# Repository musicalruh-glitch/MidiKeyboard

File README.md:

### **MIDI Keyboard**

This is my MIDI Keyboard, as per the guide from Halflife! The file called "Production" has everything necessary for JLCPCB production. As for the rest of the files, the one that end in _pcb is my PCB, _sch is my schematic, and _pro is the whole project. 

 ### **!!IMPORTANT!!**

I'm extremely sorry for the reviewers, my sister took my computer and posted a kindness reel for my closing reel, and she messed up a lot of stuff and I had to hassle with her a lot, so there wasn't a lot of time to submit properly.

Some pictures of my work:

I gave myself a challenge, for each Hack Club hardware design I make, I'll try to incorporate the Undertale hearts somehow on my PCB's! (Maybe only for Halflife actually..)
I ran into huge problems routing for this project, but I really learned a lot more than I thought I would from it. Hopefully things work out.

### **Here's what each part does!**

1. Waveshare ESP32-S3 Zero (Microcontroller)
   - This is just the microcontroller of the board, it processes the inputs and runs custom code.
2. Kalih Choc Low-Profile Switches x3
   - These are the tactile mechanical keys for the MIDI!!
3. SK6812MINI-E Addressable RGB LEDs x3
   - These are small smart lights, I'm going to solder these to the back of the PCB and they'll shine up through my board's custom cutout holes to provide glowing, customizable underglow backlighting.
4. EC11 Rotary Encoder
   - This is a dial knob that can also be pushed down like a button, awesome for adjusting volume + changing parameters or just scrolling through menus!! :D
5. Bourns Slide Potentiometer
   - This is a sliding fader knob, it connects to an analog pin to continuously measure its exact physical position making it perfect for smooth volume fades, modulation, or filter sweeps.
6. Custom 7-Pad Capacitive Touch Keys
   - This is my custom Undertale soul-heart touch interface. These copper touch pads register the electrical capacitance of my fingertips when I touch them, giving me extra touch-sensitive keys.

### **MIDI Keyboard Project Bill of Materials (BOM)**

| Part / Description | Qty | Unit Price | Total Price | Vendor | Link |
| --- | --- | --- | --- | --- | --- |
| **Custom MIDI Keyboard PCB** (Fabricated circuit board) | 1 | blank | blank | JLCPCB | blank 

* **Total Tax & Shipping for the whole order:** blank

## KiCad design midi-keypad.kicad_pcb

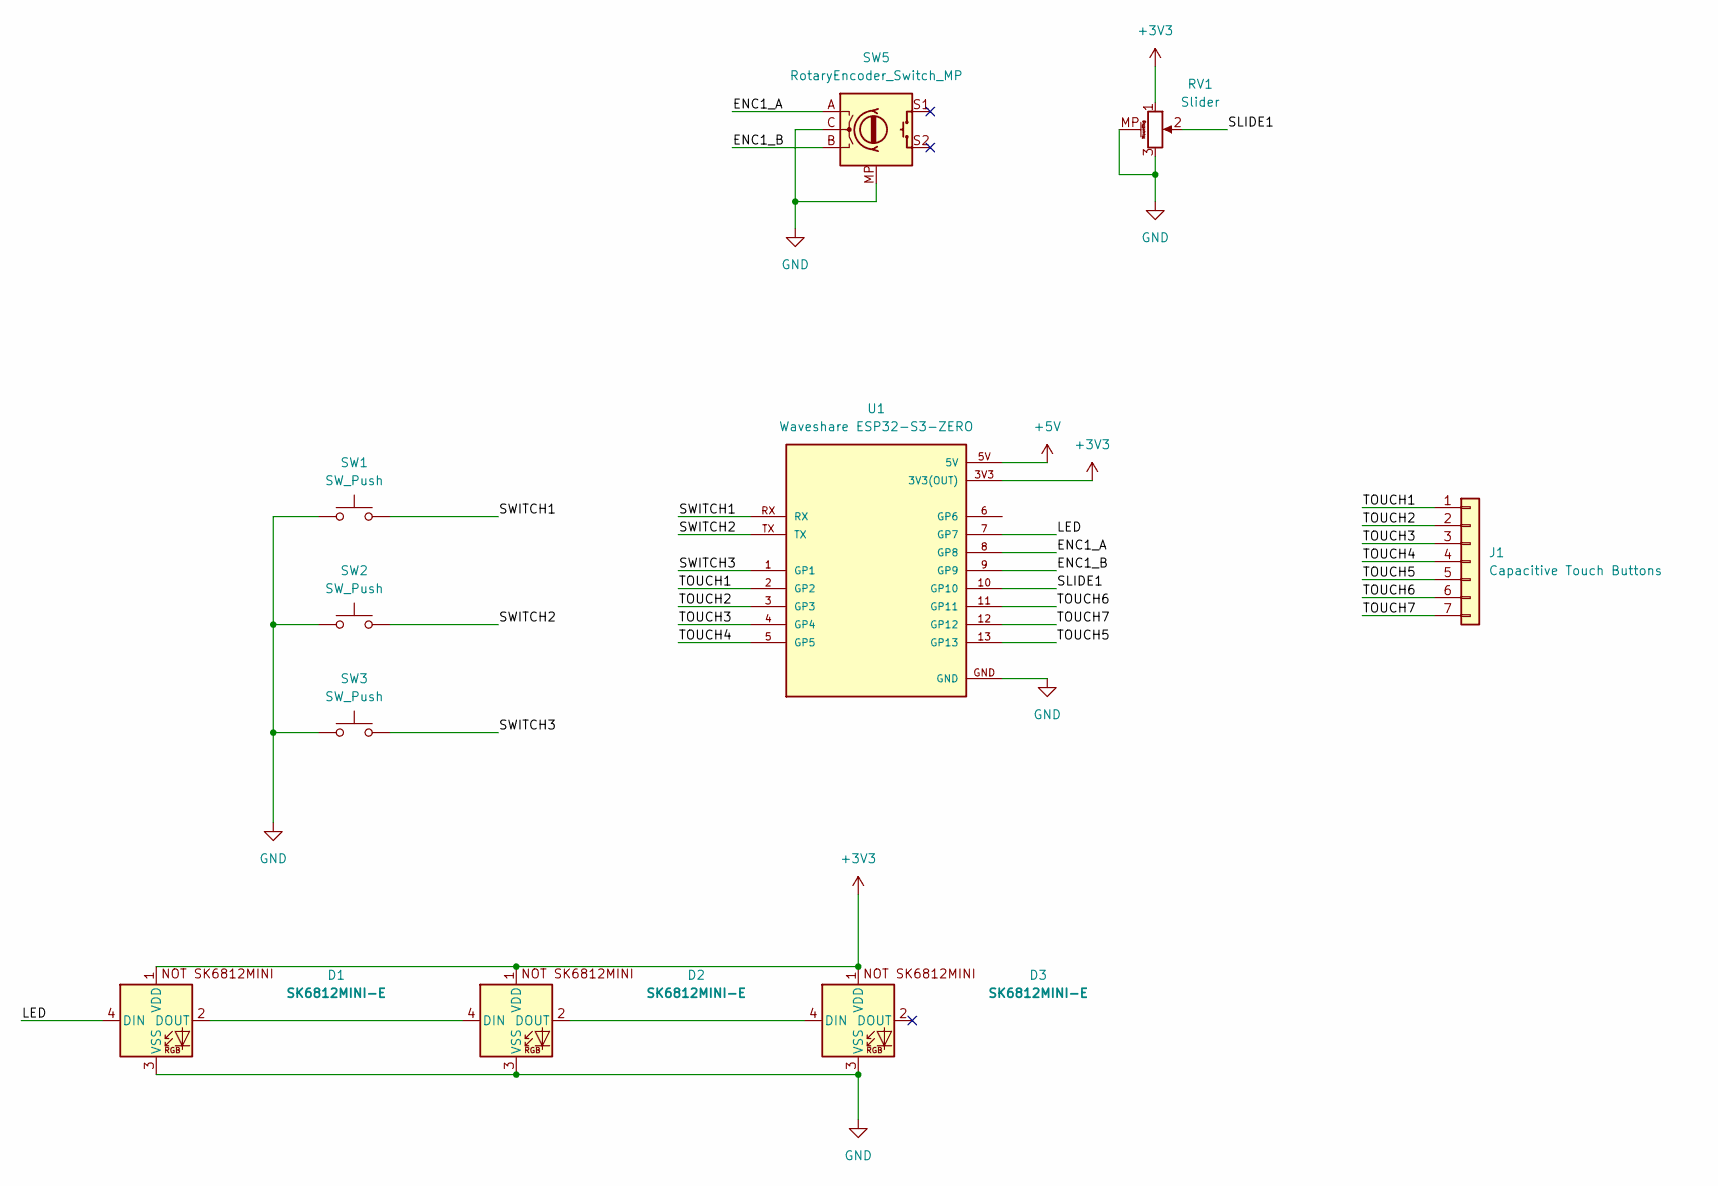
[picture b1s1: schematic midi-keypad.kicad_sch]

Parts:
D1, D2, D3: SK6812MINI-E; LED_SK6812MINI-E_3.2x2.8mm_P1.5mm_ReverseMount
J1: Capacitive Touch Buttons; CapacitiveKeys
RV1: Slider; Potentiometer_Bourns_PTA1543_Single_Slide
SW1, SW2, SW3: SW_Push; Kailh Choc Low-Profile Switches
SW5: RotaryEncoder_Switch_MP; RotaryEncoder_Alps_EC12E-Switch_Vertical_H20mm
U1: Waveshare ESP32-S3-ZERO; Waveshare ESP32-S3-Zero; PARTREV NA

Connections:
+3V3: D1.1 (VDD), D2.1 (VDD), D3.1 (VDD), RV1.1, U1.3V3 (3V3(OUT))
+5V: U1.5V
/ENC1_A: SW5.A, U1.8 (GP8)
/ENC1_B: SW5.B, U1.9 (GP9)
/LED: D1.4 (DIN), U1.7 (GP7)
/SLIDE1: RV1.2, U1.10 (GP10)
/SWITCH1: SW1.2, U1.RX
/SWITCH2: SW2.2, U1.TX
/SWITCH3: SW3.2, U1.1 (GP1)
/TOUCH1: J1.1, U1.2 (GP2)
/TOUCH2: J1.2, U1.3 (GP3)
/TOUCH3: J1.3, U1.4 (GP4)
/TOUCH4: J1.4, U1.5 (GP5)
/TOUCH5: J1.5, U1.13 (GP13)
/TOUCH6: J1.6, U1.11 (GP11)
/TOUCH7: J1.7, U1.12 (GP12)
GND: D1.3 (VSS), D2.3 (VSS), D3.3 (VSS), RV1.3, RV1.MP (MountPin), SW1.1, SW2.1, SW3.1, SW5.C, SW5.MP, U1.GND
unnamed: D1.2 (DOUT), D2.4 (DIN)
unnamed: D2.2 (DOUT), D3.4 (DIN)

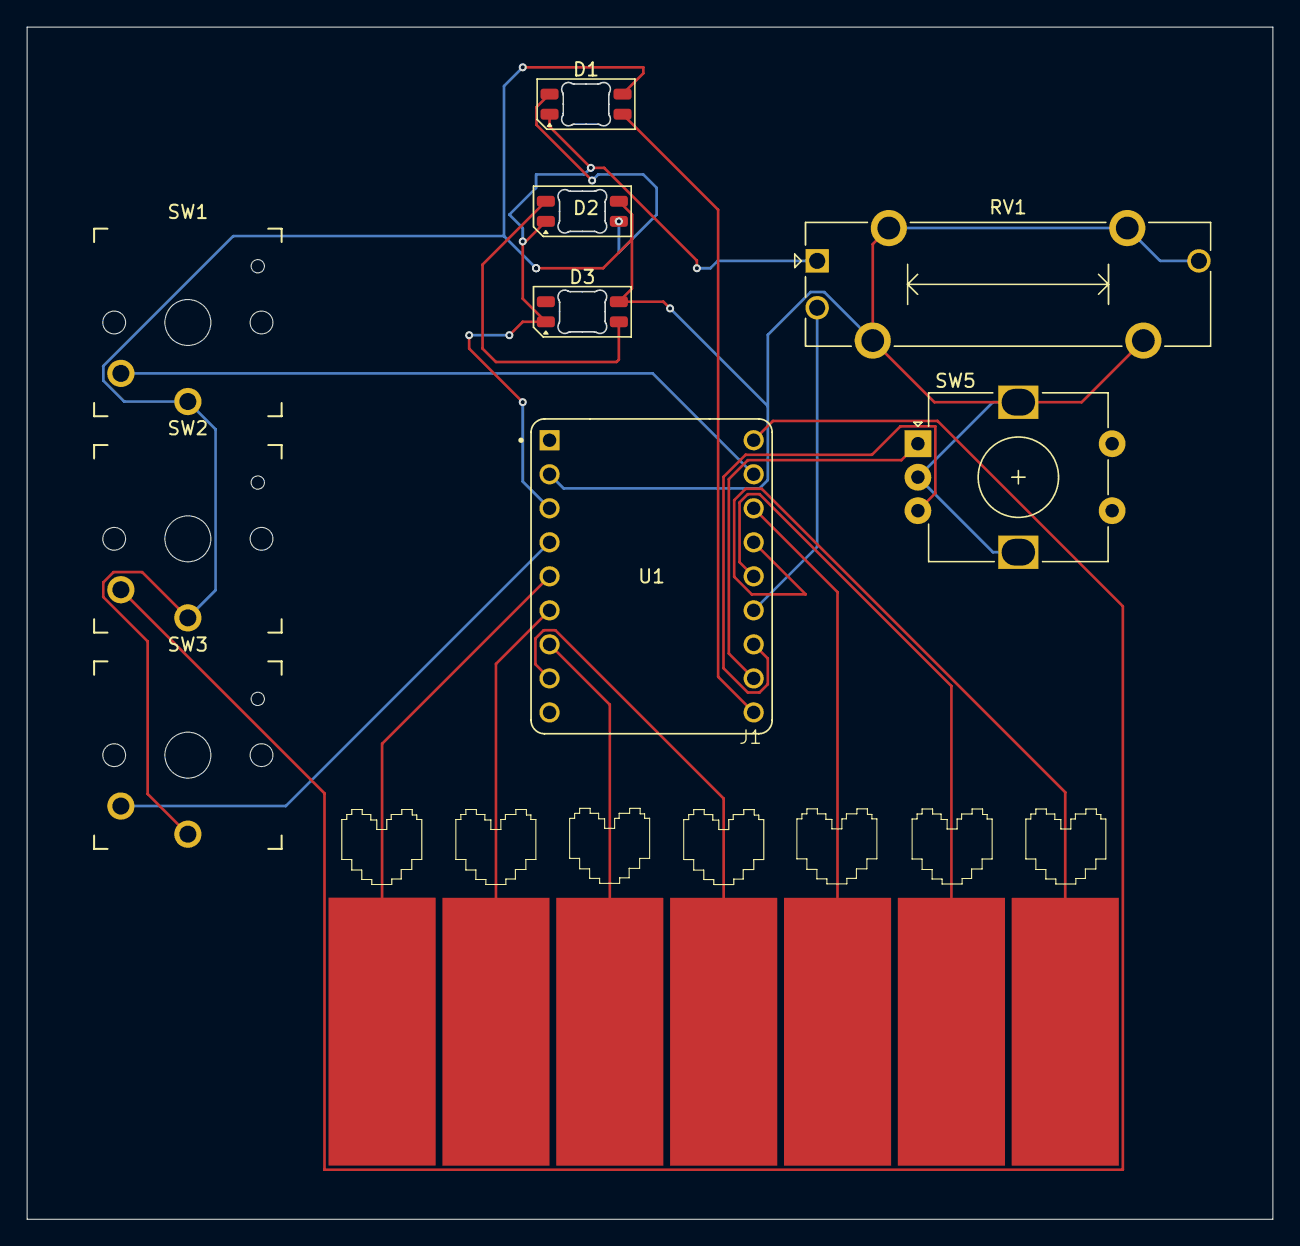
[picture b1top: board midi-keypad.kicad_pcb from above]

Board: 2 copper layers, 93.0 x 89.0 mm, 10 parts (0 on the bottom side), 18 nets.

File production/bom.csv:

Designator,Footprint,Quantity,Value,LCSC Part #
"D1, D2, D3",LED_SK6812MINI-E_3.2x2.8mm_P1.5mm_ReverseMount,3,SK6812MINI-E,
J1,CapacitiveKeys,1,Capacitive Touch Buttons,
RV1,Potentiometer_Bourns_PTA1543_Single_Slide,1,Slider,
"SW1, SW2, SW3",Kailh Choc Low-Profile Switches,3,SW_Push,
SW5,RotaryEncoder_Alps_EC12E-Switch_Vertical_H20mm,1,RotaryEncoder_Switch_MP,
U1,Waveshare ESP32-S3-Zero,1,Waveshare ESP32-S3-ZERO,
